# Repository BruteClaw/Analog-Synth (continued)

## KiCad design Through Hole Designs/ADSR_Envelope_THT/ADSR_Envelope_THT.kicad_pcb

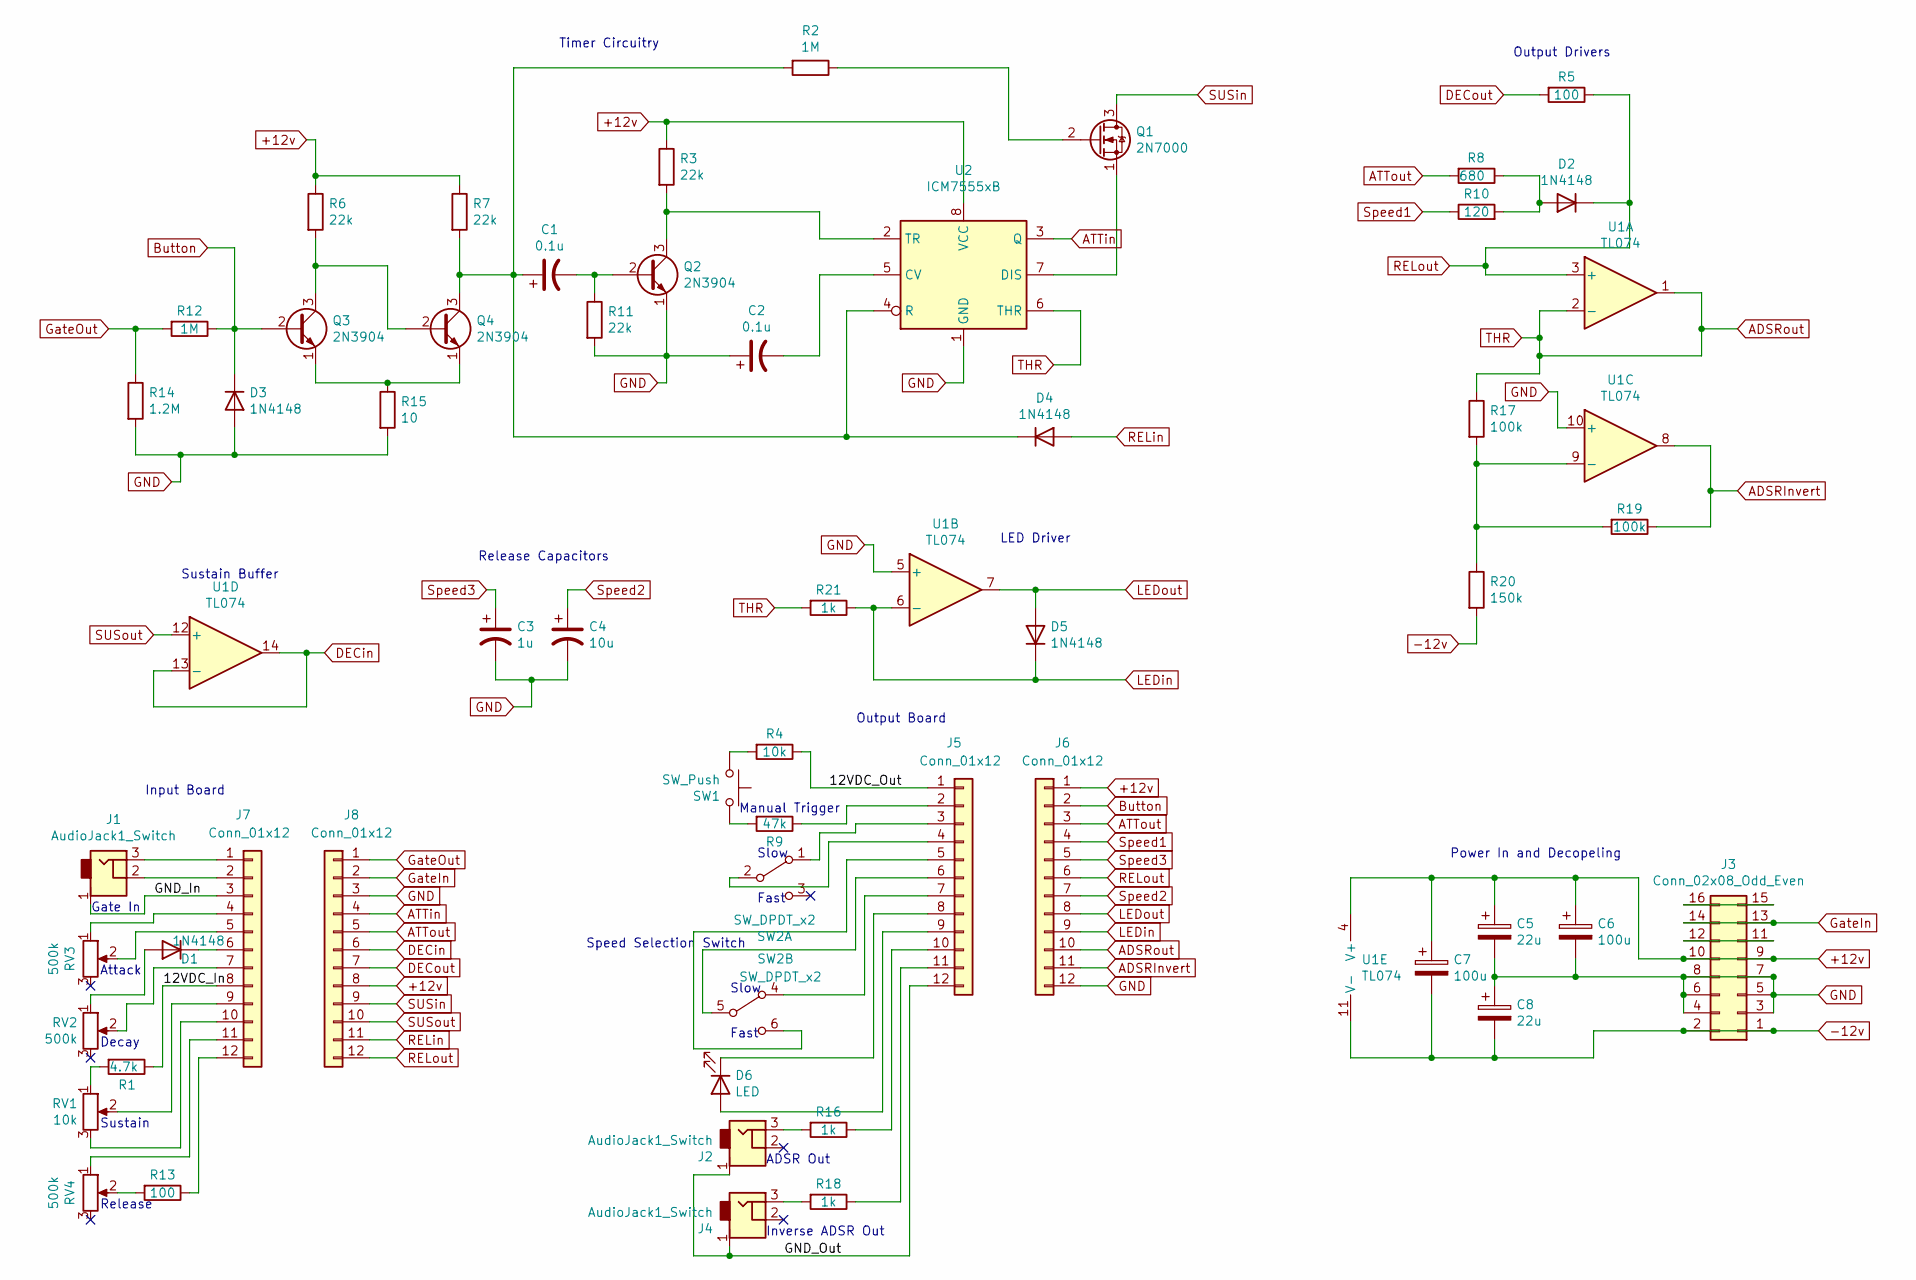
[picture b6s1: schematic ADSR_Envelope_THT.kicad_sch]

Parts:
C1, C2: 0.1u; C_Disc_D5.0mm_W2.5mm_P5.00mm
C3: 1u; C_Disc_D5.0mm_W2.5mm_P5.00mm
C4: 10u; C_Disc_D5.0mm_W2.5mm_P5.00mm
C5, C8: 22u; CP_Radial_D5.0mm_P2.00mm
C6, C7: 100u; CP_Radial_D6.3mm_P2.50mm
D1, D2, D3, D4, D5: 1N4148; D_DO-35_SOD27_P7.62mm_Horizontal
D6: LED; LED_Rectangular_W3.9mm_H1.9mm
J1, J2, J4: AudioJack1_Switch; Mono_Jack_3.5mm_Switch_Switchcraft_35RAPC2AH3
J3: Conn_02x08_Odd_Even; Pin_Header_Straight_2x08_Pitch2.54mm
J5, J6, J7, J8: Conn_01x12; Pin_Header_Straight_1x12_Pitch2.54mm
Q1: 2N7000; TO-92_Inline_Wide
Q2, Q3, Q4: 2N3904; TO-92_Inline_Wide
R1: 4.7k; R_Axial_DIN0207_L6.3mm_D2.5mm_P10.16mm_Horizontal
R2, R12: 1M; R_Axial_DIN0207_L6.3mm_D2.5mm_P10.16mm_Horizontal
R3, R6, R7, R11: 22k; R_Axial_DIN0207_L6.3mm_D2.5mm_P10.16mm_Horizontal
R4: 10k; R_Axial_DIN0207_L6.3mm_D2.5mm_P10.16mm_Horizontal
R5, R13: 100; R_Axial_DIN0207_L6.3mm_D2.5mm_P10.16mm_Horizontal
R8: 680; R_Axial_DIN0207_L6.3mm_D2.5mm_P10.16mm_Horizontal
R9: 47k; R_Axial_DIN0207_L6.3mm_D2.5mm_P10.16mm_Horizontal
R10: 120; R_Axial_DIN0207_L6.3mm_D2.5mm_P10.16mm_Horizontal
R14: 1.2M; R_Axial_DIN0207_L6.3mm_D2.5mm_P10.16mm_Horizontal
R15: 10; R_Axial_DIN0207_L6.3mm_D2.5mm_P10.16mm_Horizontal
R16, R18, R21: 1k; R_Axial_DIN0207_L6.3mm_D2.5mm_P10.16mm_Horizontal
R17, R19: 100k; R_Axial_DIN0207_L6.3mm_D2.5mm_P10.16mm_Horizontal
R20: 150k; R_Axial_DIN0207_L6.3mm_D2.5mm_P10.16mm_Horizontal
RV1: 10k; Potentiometer_Bourns_PTV09A-2_Vertical
RV2, RV3, RV4: 500k; Potentiometer_Bourns_PTV09A-2_Vertical
SW1: SW_Push; SW_Tactile_TE_FSMRACDAH
SW2: SW_DPDT_x2; 200AWMDP1T2A1M6QE
U1: TL074; DIP-14_W7.62mm_Socket
U2: ICM7555xB; DIP-8_W7.62mm_Socket

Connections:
+12v: C5.1, C6.1, C7.1, J3.9, J3.10, J6.1, J8.8, R3.1, R6.1, R7.1, U1.4 (V+), U2.8 (VCC)
-12v: C7.2, C8.2, J3.1, J3.2, R20.2, U1.11 (V-)
/12VDC_In: J7.8, R1.1
/12VDC_Out: J5.1, R4.1
/GND_In: J1.1, J7.3
/GND_Out: J2.1, J4.1, J5.12
ADSRInvert: J6.11, R19.1, U1.8
ADSRout: J6.10, R17.1, R21.2, U1.1, U1.2 (-), U2.6 (THR)
ATTin: J8.4, U2.3 (Q)
ATTout: J6.3, J8.5, R8.2
Button: D3.1 (K), J6.2, Q3.2 (B), R12.1
DECin: J8.6, U1.13 (-), U1.14
DECout: J8.7, R5.2
GND: C2.1, C3.2, C4.2, C5.2, C6.2, C8.1, D3.2 (A), J3.3, J3.4, J3.5, J3.6, J3.7, J3.8, J6.12, J8.3, Q2.1 (E), R11.2, R14.2, R15.2, U1.5 (+), U1.10 (+), U2.1 (GND)
GateIn: J3.13, J3.14, J8.2
GateOut: J8.1, R12.2, R14.1
LEDin: D5.1 (K), J6.9, R21.1, U1.6 (-)
LEDout: D5.2 (A), J6.8, U1.7
unnamed: C1.1, D4.1 (K), Q4.3 (C), R2.2, R7.2, U2.4 (R)
unnamed: C1.2, Q2.2 (B), R11.1
unnamed: C2.2, U2.5 (CV)
unnamed: D1.1 (K), J7.6
unnamed: D1.2 (A), RV2.1
unnamed: D2.2 (A), R8.1, R10.2
unnamed: D6.1 (K), J5.8
unnamed: D6.2 (A), J5.9
unnamed: J1.2, J7.2
unnamed: J1.3, J7.1
unnamed: J2.3, R16.2
unnamed: J3.11, J3.12
unnamed: J3.15, J3.16
unnamed: J4.3, R18.2
unnamed: J5.2, R9.1
unnamed: J5.3, SW2.1 (A)
unnamed: J5.4, SW2.2 (B)
unnamed: J5.5, SW2.6 (C)
unnamed: J5.6, SW2.5 (B)
unnamed: J5.7, SW2.4 (A)
unnamed: J5.10, R16.1
unnamed: J5.11, R18.1
unnamed: J7.4, RV3.1
unnamed: J7.5, RV3.2
unnamed: J7.7, RV2.2
unnamed: J7.9, RV1.2
unnamed: J7.10, RV1.3
unnamed: J7.11, RV4.1
unnamed: J7.12, R13.1
unnamed: Q1.1 (S), U2.7 (DIS)
unnamed: Q1.2 (G), R2.1
unnamed: Q2.3 (C), R3.2, U2.2 (TR)
unnamed: Q3.1 (E), Q4.1 (E), R15.1
unnamed: Q3.3 (C), Q4.2 (B), R6.2
unnamed: R1.2, RV1.1
unnamed: R4.2, SW1.1
unnamed: R9.2, SW1.2
unnamed: R13.2, RV4.2
unnamed: R17.2, R19.2, R20.1, U1.9 (-)
RELin: D4.2 (A), J8.11
RELout: D2.1 (K), J6.6, J8.12, R5.1, U1.3 (+)
SUSin: J8.9, Q1.3 (D)
SUSout: J8.10, U1.12 (+)
Speed1: J6.4, R10.1
Speed2: C4.1, J6.7
Speed3: C3.1, J6.5

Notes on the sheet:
Timer Circuitry
ADSR Out
Attack
Sustain
Gate In
Input Board
Output Drivers
Fast
Sustain Buffer
Slow
Release
Inverse ADSR Out
Power In and Decopeling
LED Driver
Speed Selection Switch
Manual Trigger
Output Board
Decay
Release Capacitors

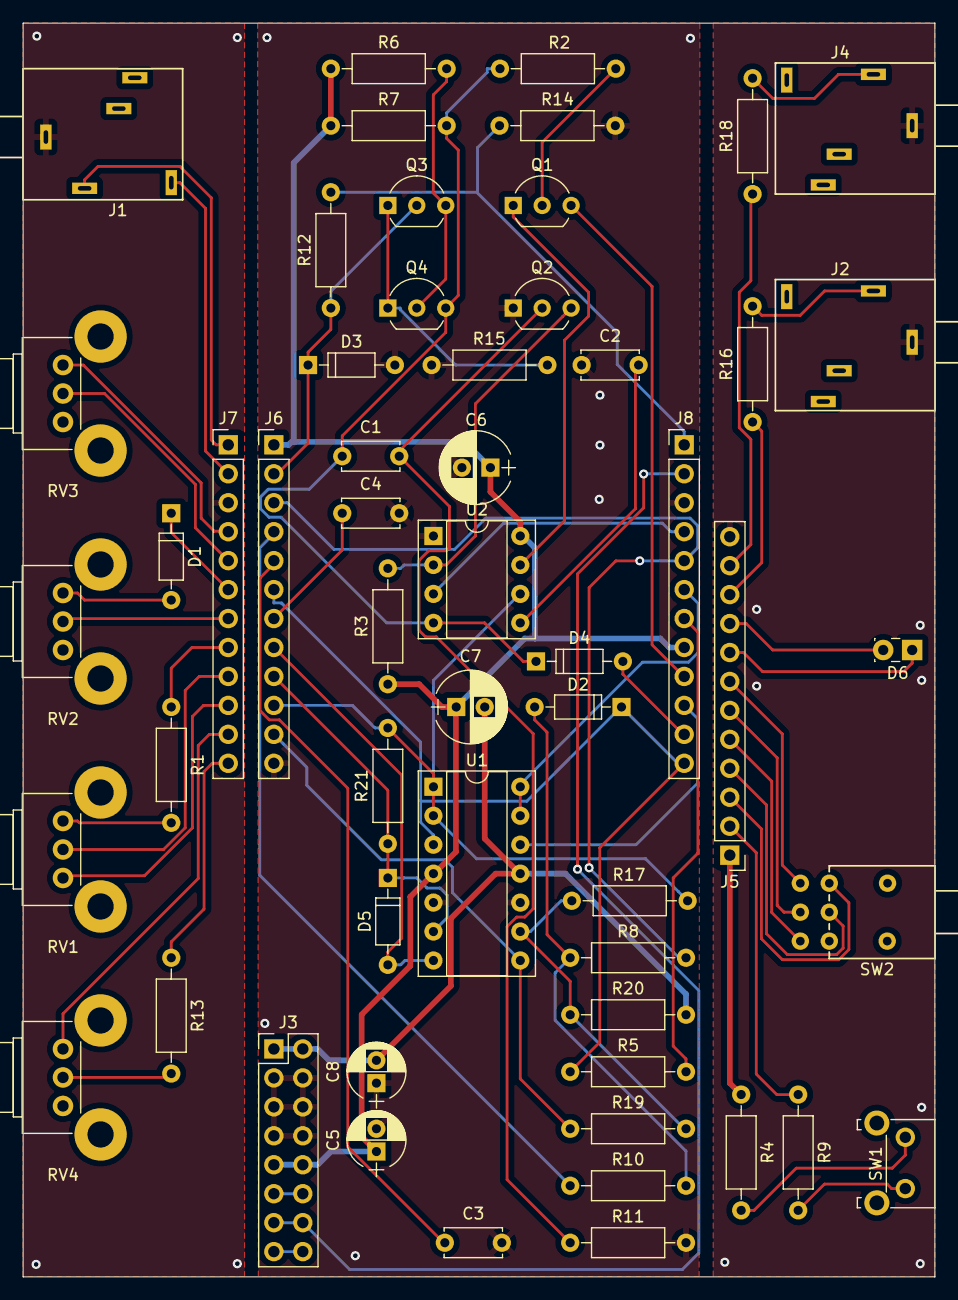
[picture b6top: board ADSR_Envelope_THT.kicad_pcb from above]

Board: 2 copper layers, 80.0 x 110.0 mm, 55 parts (0 on the bottom side), 64 nets.
